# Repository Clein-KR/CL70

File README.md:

# CL70

<br />

CL70은 제가 자작을 시도하며 처음 만들었던 키보드입니다.

아무것도 모르는 채로 시작하여 겪어야 했던 수 많은 시행 착오를 다른 분들은 최대한 줄였으면 하는 마음에 해당 키보드를 리메이크 하는 내용으로 [나만의 커스텀 커스텀 키보드 만들기 시리즈](https://www.notion.so/clein-kr/27f2e6fbea69806facf0daf639f351d5)를 노션에 연재해 두었으니 자작 키보드에 관심이 있으신 분들은 한 번 읽어 보시는 것을 추천 드립니다.

<br />
<br />

**Silver Top**

<br />

**Black Top**

<br />
<br />

## Licence

<br />

작업물에 대한 영리적 목적의 사용 및 재배포는 허용하지 않으며, 비영리적 활동에만 사용 및 출처를 포함한 재배포를 허용합니다. 또한 작업물에 만약 오류나 문제가 있더라도 원작자는 이에 대해 어떠한 책임도 지지 않음을 미리 밝힙니다. 라이선스 전문은 [여기](./LICENCE)에서 보실 수 있습니다.

<br />
<br />

© 2026 [Clein](https://github.com/Clein-KR) All Rights Reserved. Licensed under [CC BY-NC 4.0](https://creativecommons.org/licenses/by-nc/4.0/)

<br />

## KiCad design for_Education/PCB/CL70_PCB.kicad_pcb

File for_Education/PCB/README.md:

# CL70 PCB for Education

<br />

<br />
<br />

## Licence

<br />

해당 프로젝트는 [ai03](https://github.com/ai03-2725) 님의 [KBD8X-MKII-PCB](https://github.com/ai03-2725/KBD8X-MKII-PCB) 프로젝트와 [Joe Scotto](https://github.com/joe-scotto) 님의 [ScottoKeebs](https://github.com/joe-scotto/scottokeebs) 프로젝트를 기반으로 만들어졌습니다. 해당 프로젝트를 활용한 수정, 복제, 배포 등의 활동은 저작자 표시와 함께 비영리적인 목적에 한해서만 가능하며, 라이선스 전문은 [여기](./LICENCE)에서 보실 수 있습니다.

<br />

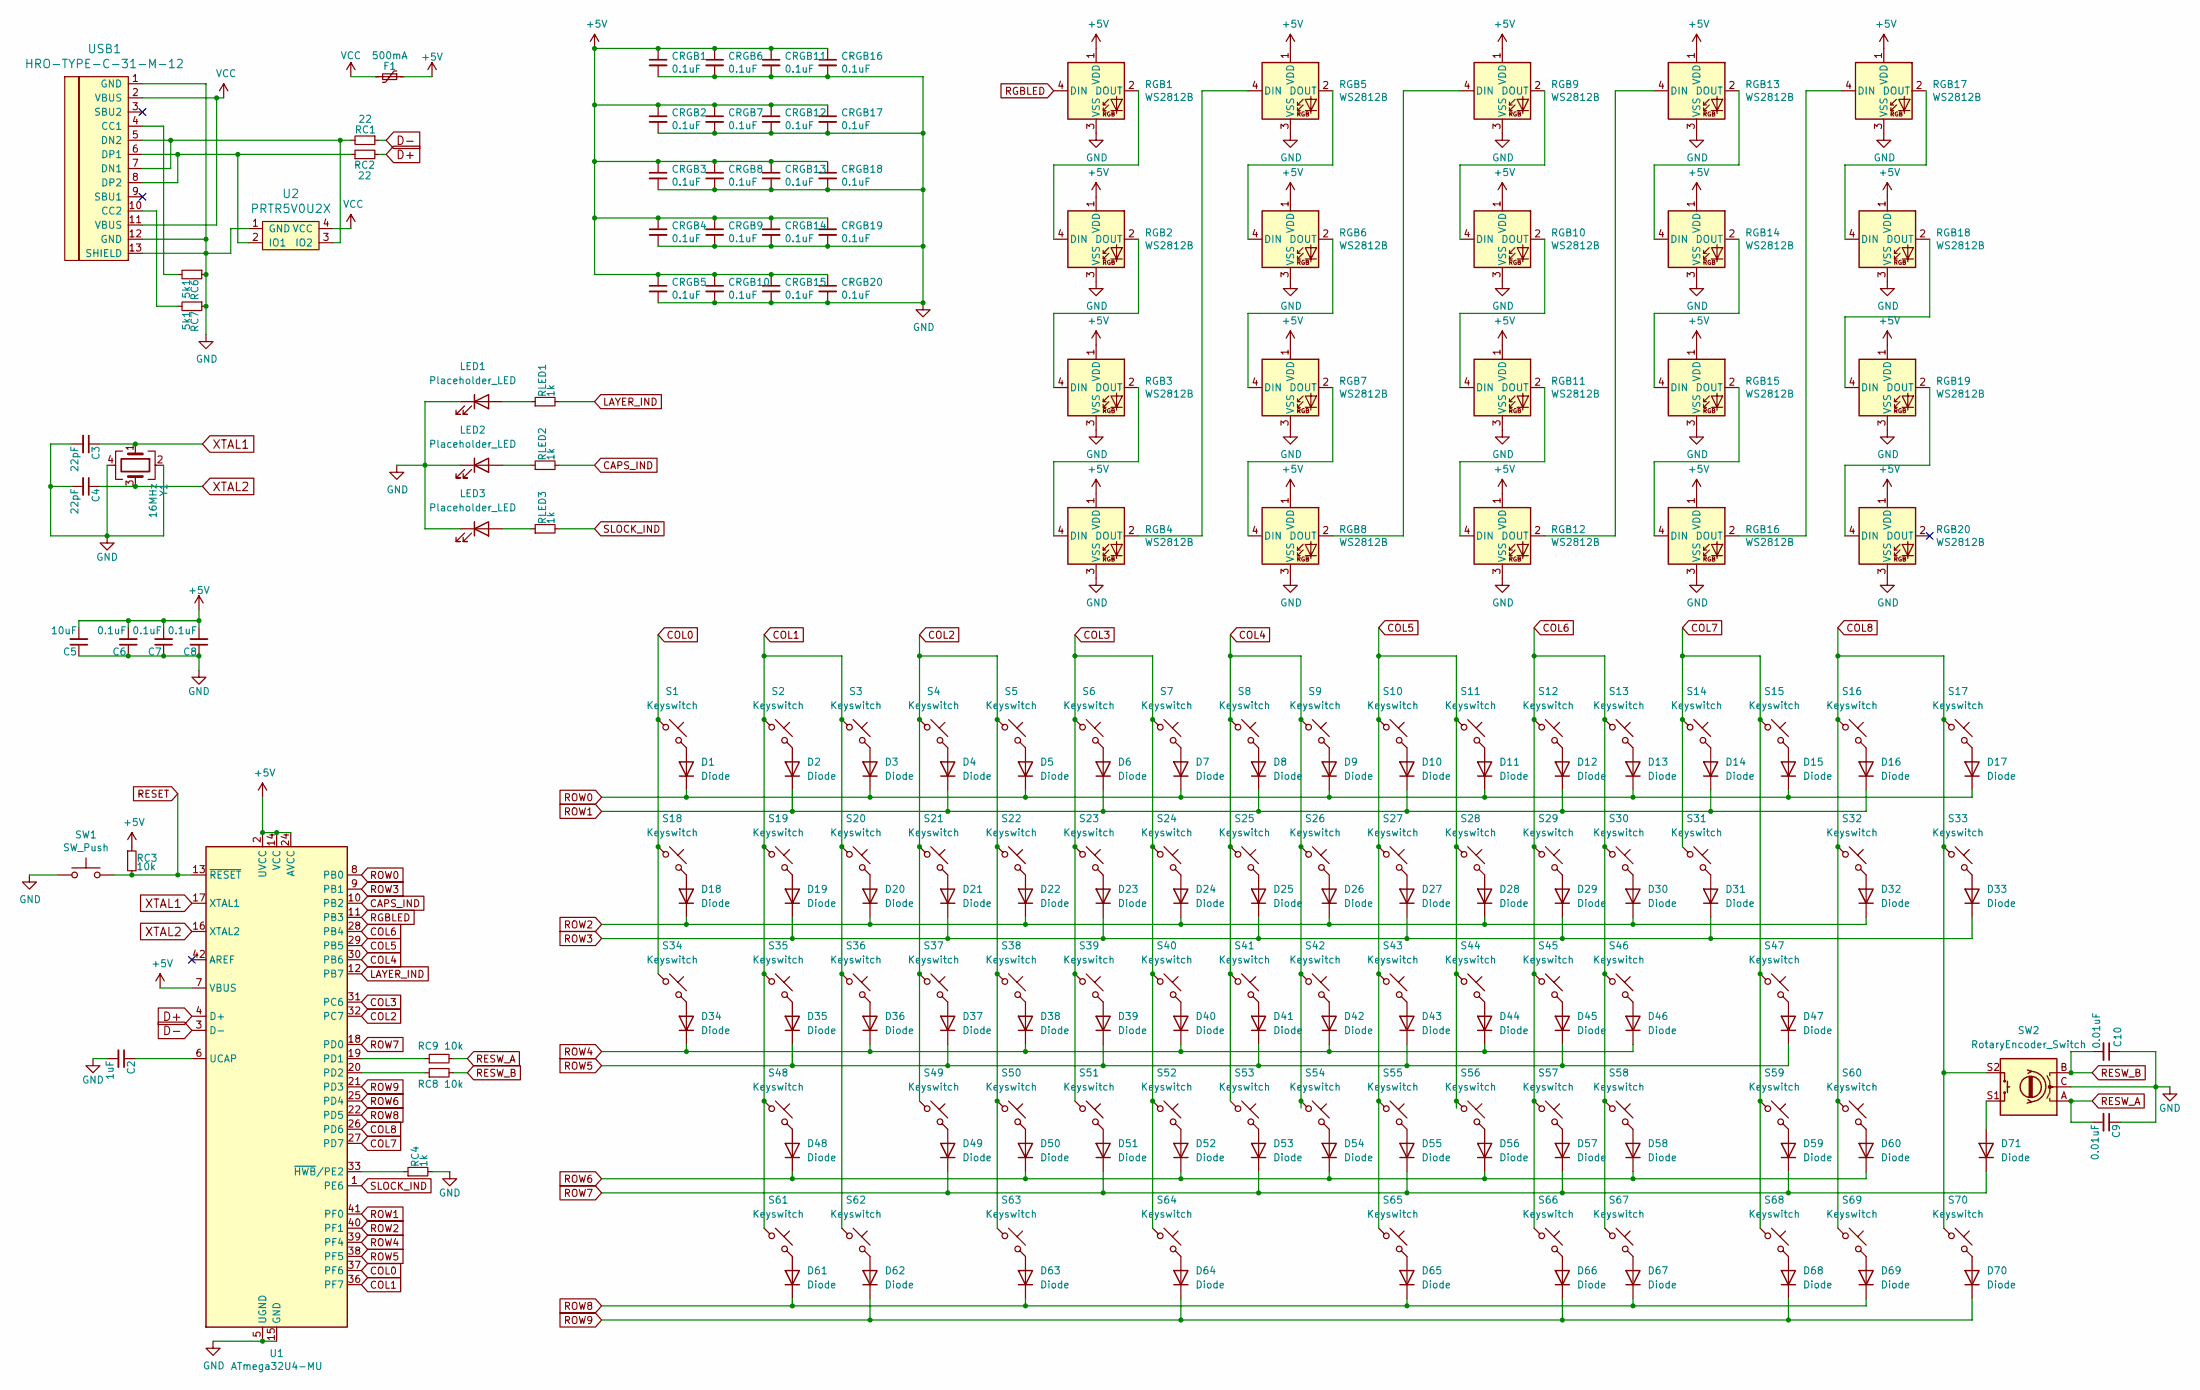
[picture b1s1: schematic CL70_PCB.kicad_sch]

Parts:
C2: 1uF; C_0603
C3, C4: 22pF; C_0603
C5: 10uF; C_0603
C6, C7, C8: 0.1uF; C_0603
C9, C10: 0.01uF; C_0603
CRGB1, CRGB2, CRGB3, CRGB4, CRGB5, CRGB6, CRGB7, CRGB8, CRGB9, CRGB10, CRGB11, CRGB12, CRGB13, CRGB14, CRGB15, CRGB16, CRGB17, CRGB18, CRGB19, CRGB20: 0.1uF; C_0603
D1, D2, D3, D4, D5, D6, D7, D8, D9, D10, D11, D12, D13, D14, D15, D16, D17, D18, D19, D20, D21, D22, D23, D24, D25, D26, D27, D28, D29, D30, D31, D32, D33, D34, D35, D36, D37, D38, D39, D40, D41, D42, D43, D44, D45, D46, D47, D48, D49, D50, D51, D52, D53, D54, D55, D56, D57, D58, D59, D60, D61, D62, D63, D64, D65, D66, D67, D68, D69, D70, D71: Diode; D_SOD-123
F1: 500mA; Fuse_1206_3216Metric
LED1, LED2, LED3: Placeholder_LED; LED_D3.0mm-Pretty
RC1, RC2: 22; R_0603
RC3, RC8, RC9: 10k; R_0603
RC4: 1k; R_0603
RC6, RC7: 5k1; R_0603
RGB1, RGB2, RGB3, RGB4, RGB5, RGB6, RGB7, RGB8, RGB9, RGB10, RGB11, RGB12, RGB13, RGB14, RGB15, RGB16, RGB17, RGB18, RGB19, RGB20: WS2812B; LED_WS2812B-PLCC4
RLED1, RLED2, RLED3: 1k; R_0603
S1, S2, S3, S4, S5, S6, S7, S8, S9, S10, S11, S12, S13, S14, S15, S16, S17, S18, S20, S21, S22, S23, S24, S25, S26, S27, S28, S29, S30, S31, S33, S34, S36, S37, S38, S39, S40, S41, S42, S43, S44, S45, S46, S49, S50, S51, S52, S53, S54, S55, S56, S57, S58, S60, S68, S69, S70: Keyswitch; MX_PCB_1.00u
S19, S32, S63, S66: Keyswitch; MX_PCB_1.50u
S35: Keyswitch; MX_PCB_1.75u
S47, S48: Keyswitch; Hotswap_MX_2.25u
S59: Keyswitch; Hotswap_MX_2.00u
S61, S62, S67: Keyswitch; MX_PCB_1.25u
S64, S65: Keyswitch; Hotswap_MX_3.00u
SW1: SW_Push; SKQG-1155865
SW2: RotaryEncoder_Switch; RotaryEncoder_Alps_EC11E-Switch_Vertical_H20mm
U1: ATmega32U4-MU; QFN-44-1EP_7x7mm_Pitch0.5mm
U2: PRTR5V0U2X; SOT143B
USB1: HRO-TYPE-C-31-M-12; HRO-TYPE-C-31-M-12-Assembly
Y1: 16MHz; Crystal_SMD_3225-4pin_3.2x2.5mm

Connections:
+5V: C5.2, C6.2, C7.2, C8.2, CRGB1.1, CRGB2.1, CRGB3.1, CRGB4.1, CRGB5.1, CRGB6.1, CRGB7.1, CRGB8.1, CRGB9.1, CRGB10.1, CRGB11.1, CRGB12.1, CRGB13.1, CRGB14.1, CRGB15.1, CRGB16.1, CRGB17.1, CRGB18.1, CRGB19.1, CRGB20.1, F1.1, RC3.1, RGB1.1 (VDD), RGB2.1 (VDD), RGB3.1 (VDD), RGB4.1 (VDD), RGB5.1 (VDD), RGB6.1 (VDD), RGB7.1 (VDD), RGB8.1 (VDD), RGB9.1 (VDD), RGB10.1 (VDD), RGB11.1 (VDD), RGB12.1 (VDD), RGB13.1 (VDD), RGB14.1 (VDD), RGB15.1 (VDD), RGB16.1 (VDD), RGB17.1 (VDD), RGB18.1 (VDD), RGB19.1 (VDD), RGB20.1 (VDD), U1.2 (UVCC), U1.7 (VBUS), U1.14 (VCC), U1.24 (AVCC), U1.34 (VCC), U1.44 (AVCC)
CAPS_IND: RLED2.2, U1.10 (PB2)
COL0: S1.1, S18.1, S34.1, U1.37 (PF6)
COL1: S2.1, S3.1, S19.1, S20.1, S35.1, S36.1, S48.1, S61.1, S62.1, U1.36 (PF7)
COL2: S4.1, S5.1, S21.1, S22.1, S37.1, S38.1, S49.1, S50.1, S63.1, U1.32 (PC7)
COL3: S6.1, S7.1, S23.1, S24.1, S39.1, S40.1, S51.1, S52.1, S64.1, U1.31 (PC6)
COL4: S8.1, S9.1, S25.1, S26.1, S41.1, S42.1, S53.1, S54.1, U1.30 (PB6)
COL5: S10.1, S11.1, S27.1, S28.1, S43.1, S44.1, S55.1, S56.1, S65.1, U1.29 (PB5)
COL6: S12.1, S13.1, S29.1, S30.1, S45.1, S46.1, S57.1, S58.1, S66.1, S67.1, U1.28 (PB4)
COL7: S14.1, S15.1, S31.1, S47.1, S59.1, S68.1, U1.27 (PD7)
COL8: S16.1, S17.1, S32.1, S33.1, S60.1, S69.1, S70.1, SW2.S2, U1.26 (PD6)
D+: RC2.2, U1.4 (D+)
D-: RC1.1, U1.3 (D-)
GND: C2.2, C3.2, C4.2, C5.1, C6.1, C7.1, C8.1, C9.1, C10.1, CRGB1.2, CRGB2.2, CRGB3.2, CRGB4.2, CRGB5.2, CRGB6.2, CRGB7.2, CRGB8.2, CRGB9.2, CRGB10.2, CRGB11.2, CRGB12.2, CRGB13.2, CRGB14.2, CRGB15.2, CRGB16.2, CRGB17.2, CRGB18.2, CRGB19.2, CRGB20.2, LED1.1 (K), LED2.1 (K), LED3.1 (K), RC4.2, RC6.1, RC7.1, RGB1.3 (VSS), RGB2.3 (VSS), RGB3.3 (VSS), RGB4.3 (VSS), RGB5.3 (VSS), RGB6.3 (VSS), RGB7.3 (VSS), RGB8.3 (VSS), RGB9.3 (VSS), RGB10.3 (VSS), RGB11.3 (VSS), RGB12.3 (VSS), RGB13.3 (VSS), RGB14.3 (VSS), RGB15.3 (VSS), RGB16.3 (VSS), RGB17.3 (VSS), RGB18.3 (VSS), RGB19.3 (VSS), RGB20.3 (VSS), SW1.1, SW2.C, U1.5 (UGND), U1.15 (GND), U1.23 (GND), U1.35 (GND), U1.43 (GND), U1.45 (GND), U2.1 (GND), USB1.1 (GND), USB1.12 (GND), USB1.13 (SHIELD), Y1.2, Y1.4
LAYER_IND: RLED1.2, U1.12 (PB7)
unnamed: D1.2 (A), S1.2
unnamed: D2.2 (A), S2.2
unnamed: D3.2 (A), S3.2
unnamed: D4.2 (A), S4.2
unnamed: D5.2 (A), S5.2
unnamed: D6.2 (A), S6.2
unnamed: D7.2 (A), S7.2
unnamed: D8.2 (A), S8.2
unnamed: D9.2 (A), S9.2
unnamed: D10.2 (A), S10.2
unnamed: D11.2 (A), S11.2
unnamed: D12.2 (A), S12.2
unnamed: D13.2 (A), S13.2
unnamed: D14.2 (A), S14.2
unnamed: D15.2 (A), S15.2
unnamed: D16.2 (A), S16.2
unnamed: D17.2 (A), S17.2
unnamed: D18.2 (A), S18.2
unnamed: D19.2 (A), S19.2
unnamed: D20.2 (A), S20.2
unnamed: D21.2 (A), S21.2
unnamed: D22.2 (A), S22.2
unnamed: D23.2 (A), S23.2
unnamed: D24.2 (A), S24.2
unnamed: D25.2 (A), S25.2
unnamed: D26.2 (A), S26.2
unnamed: D27.2 (A), S27.2
unnamed: D28.2 (A), S28.2
unnamed: D29.2 (A), S29.2
unnamed: D30.2 (A), S30.2
unnamed: D31.2 (A), S31.2
unnamed: D32.2 (A), S32.2
unnamed: D33.2 (A), S33.2
unnamed: D34.2 (A), S34.2
unnamed: D35.2 (A), S35.2
unnamed: D36.2 (A), S36.2
unnamed: D37.2 (A), S37.2
unnamed: D38.2 (A), S38.2
unnamed: D39.2 (A), S39.2
unnamed: D40.2 (A), S40.2
unnamed: D41.2 (A), S41.2
unnamed: D42.2 (A), S42.2
unnamed: D43.2 (A), S43.2
unnamed: D44.2 (A), S44.2
unnamed: D45.2 (A), S45.2
unnamed: D46.2 (A), S46.2
unnamed: D47.2 (A), S47.2
unnamed: D48.2 (A), S48.2
unnamed: D49.2 (A), S49.2
unnamed: D50.2 (A), S50.2
unnamed: D51.2 (A), S51.2
unnamed: D52.2 (A), S52.2
unnamed: D53.2 (A), S53.2
unnamed: D54.2 (A), S54.2
unnamed: D55.2 (A), S55.2
unnamed: D56.2 (A), S56.2
unnamed: D57.2 (A), S57.2
unnamed: D58.2 (A), S58.2
unnamed: D59.2 (A), S59.2
unnamed: D60.2 (A), S60.2
unnamed: D61.2 (A), S61.2
unnamed: D62.2 (A), S62.2
unnamed: D63.2 (A), S63.2
unnamed: D64.2 (A), S64.2
unnamed: D65.2 (A), S65.2
unnamed: D66.2 (A), S66.2
unnamed: D67.2 (A), S67.2
unnamed: D68.2 (A), S68.2
unnamed: D69.2 (A), S69.2
unnamed: D70.2 (A), S70.2
unnamed: D71.2 (A), SW2.S1
unnamed: LED1.2 (A), RLED1.1
unnamed: LED2.2 (A), RLED2.1
unnamed: LED3.2 (A), RLED3.1
unnamed: RGB1.2 (DOUT), RGB2.4 (DIN)
unnamed: RGB2.2 (DOUT), RGB3.4 (DIN)
unnamed: RGB3.2 (DOUT), RGB4.4 (DIN)
unnamed: RGB4.2 (DOUT), RGB5.4 (DIN)
unnamed: RGB5.2 (DOUT), RGB6.4 (DIN)
unnamed: RGB6.2 (DOUT), RGB7.4 (DIN)
unnamed: RGB7.2 (DOUT), RGB8.4 (DIN)
unnamed: RGB8.2 (DOUT), RGB9.4 (DIN)
unnamed: RGB9.2 (DOUT), RGB10.4 (DIN)
unnamed: RGB10.2 (DOUT), RGB11.4 (DIN)
unnamed: RGB11.2 (DOUT), RGB12.4 (DIN)
unnamed: RGB12.2 (DOUT), RGB13.4 (DIN)
unnamed: RGB13.2 (DOUT), RGB14.4 (DIN)
unnamed: RGB14.2 (DOUT), RGB15.4 (DIN)
unnamed: RGB15.2 (DOUT), RGB16.4 (DIN)
unnamed: RGB16.2 (DOUT), RGB17.4 (DIN)
unnamed: RGB17.2 (DOUT), RGB18.4 (DIN)
unnamed: RGB18.2 (DOUT), RGB19.4 (DIN)
unnamed: RGB19.2 (DOUT), RGB20.4 (DIN)
unnamed: RC9.1, U1.19 (PD1)
unnamed: RC8.1, U1.20 (PD2)
unnamed: C2.1, U1.6 (UCAP)
unnamed: RC4.1, U1.33 (~HWB/PE2)
unnamed: RC2.1, U2.2 (IO1), USB1.6 (DP1), USB1.8 (DP2)
unnamed: RC1.2, U2.3 (IO2), USB1.5 (DN2), USB1.7 (DN1)
unnamed: RC6.2, USB1.4 (CC1)
unnamed: RC7.2, USB1.10 (CC2)
RESET: RC3.2, SW1.2, U1.13 (~RESET)
RESW_A: C9.2, RC9.2, SW2.A
RESW_B: C10.2, RC8.2, SW2.B
RGBLED: RGB1.4 (DIN), U1.11 (PB3)
ROW0: D1.1 (K), D3.1 (K), D5.1 (K), D7.1 (K), D9.1 (K), D11.1 (K), D13.1 (K), D15.1 (K), D17.1 (K), U1.8 (PB0)
ROW1: D2.1 (K), D4.1 (K), D6.1 (K), D8.1 (K), D10.1 (K), D12.1 (K), D14.1 (K), D16.1 (K), U1.41 (PF0)
ROW2: D18.1 (K), D20.1 (K), D22.1 (K), D24.1 (K), D26.1 (K), D28.1 (K), D30.1 (K), D32.1 (K), U1.40 (PF1)
ROW3: D19.1 (K), D21.1 (K), D23.1 (K), D25.1 (K), D27.1 (K), D29.1 (K), D31.1 (K), D33.1 (K), U1.9 (PB1)
ROW4: D34.1 (K), D36.1 (K), D38.1 (K), D40.1 (K), D42.1 (K), D44.1 (K), D46.1 (K), U1.39 (PF4)
ROW5: D35.1 (K), D37.1 (K), D39.1 (K), D41.1 (K), D43.1 (K), D45.1 (K), D47.1 (K), U1.38 (PF5)
ROW6: D48.1 (K), D50.1 (K), D52.1 (K), D54.1 (K), D56.1 (K), D58.1 (K), D60.1 (K), U1.25 (PD4)
ROW7: D49.1 (K), D51.1 (K), D53.1 (K), D55.1 (K), D57.1 (K), D59.1 (K), D71.1 (K), U1.18 (PD0)
ROW8: D61.1 (K), D63.1 (K), D65.1 (K), D67.1 (K), D69.1 (K), U1.22 (PD5)
ROW9: D62.1 (K), D64.1 (K), D66.1 (K), D68.1 (K), D70.1 (K), U1.21 (PD3)
SLOCK_IND: RLED3.2, U1.1 (PE6)
VCC: F1.2, U2.4 (VCC), USB1.2 (VBUS), USB1.11 (VBUS)
XTAL1: C3.1, U1.17 (XTAL1), Y1.1
XTAL2: C4.1, U1.16 (XTAL2), Y1.3

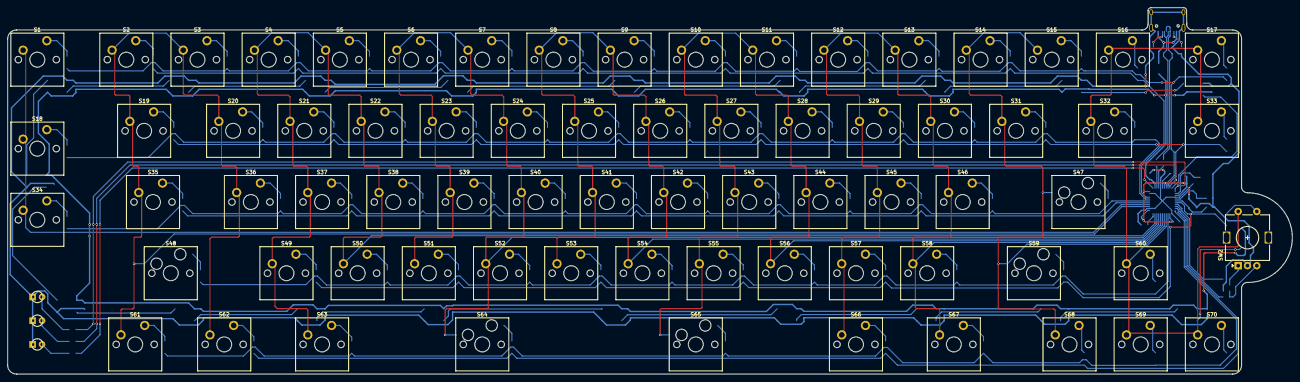
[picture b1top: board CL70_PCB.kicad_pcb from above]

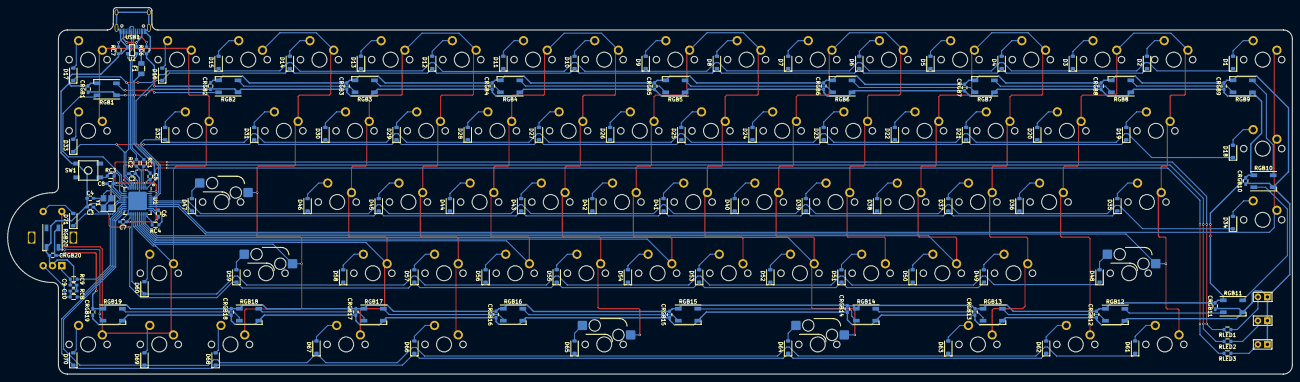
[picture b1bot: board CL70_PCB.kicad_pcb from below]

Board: 2 copper layers, 343.8 x 98.1 mm, 211 parts (137 on the bottom side), 134 nets.

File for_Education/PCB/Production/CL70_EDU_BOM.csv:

,,,,,,,,,,
,Item #,*Designator,*Qty,Manufacturer,*Mfg Part #,LCSC Part #,Description / Value,*Package/Footprint,Pins,Your Instructions / Notes
,1,"C6,C7,C8,CRGB1,CRGB2,CRGB3,CRGB4,CRGB5,CRGB6,CRGB7,CRGB8,CRGB9,CRGB10,CRGB11,CRGB12,CRGB13,CRGB14,CRGB15,CRGB16,CRGB17,CRGB18,CRGB19,CRGB20",23,YAGEO,CC0603JRX7R7BB104,C109474,"Capacitor, Ceramic, 0603",C_0603,2,0.1uF 20% ≥15V X5R/X7R
,2,C5,1,HRE,CGA0603X5R106M160JT,C6119814,"Capacitor, Ceramic, 0603",C_0603,2,10uF 20% ≥15V X5R/X7R
,3,C2,1,HRE,CGA0603X5R105K160JT,C6119849,"Capacitor, Ceramic, 0603",C_0603,2,1uF 20% ≥15V X5R/X7R
,4,"C3,C4",2,KEMET,C0603C220J4GAC7867,C561800,"Capacitor, Ceramic, 0603",C_0603,2,22pF 5% ≥15V C0G
,5,"D1,D2,D3,D4,D5,D6,D7,D8,D9,D10,D11,D12,D13,D14,D15,D16,D17,D18,D19,D20,D21,D22,D23,D24,D25,D26,D27,D28,D29,D30,D31,D32,D33,D34,D35,D36,D37,D38,D39,D40,D41,D42,D43,D44,D45,D46,D47,D48,D49,D50,D51,D52,D53,D54,D55,D56,D57,D58,D59,D60,D61,D62,D63,D64,D65,D66,D67,D68,D69,D70,D71",71,Slkor(SLKORMICRO Elec.),1N4148W,C444720,"Diode, SOD-123",D_SOD-123,2,Generic
,6,F1,1,BHFUSE,BSMD1206-050-16V,C883124,"Polyfuse, 1206",Fuse_SMD1206_Wave,2,500mA ≥15V 500mA_Hold 1A_Trip
,7,"RC4,RLED1,RLED2,RLED3",4,YAGEO,RC0603FR-071KL,C22548,"Resistor, Generic, 0603",R_0603,2,1k 1%
,8,"RC3,RC8,RC9",3,YAGEO,RC0603FR-0710KL,C98220,"Resistor, Generic, 0603",R_0603,2,10k 1%
,9,"RC1,RC2",2,YAGEO,RC0603FR-0722RL,C107701,"Resistor, Generic, 0603",R_0603,2,22 1%
,10,"RC6,RC7",2,YAGEO,RC0603FR-075K1L,C105580,"Resistor, Generic, 0603",R_0603,2,5.1k 1%
,11,"RGB1,RGB2,RGB3,RGB4,RGB5,RGB6,RGB7,RGB8,RGB9,RGB10,RGB11,RGB12,RGB13,RGB14,RGB15,RGB16,RGB17,RGB18,RGB19,RGB20",20,Worldsemi,WS2812B-V5/W,C2874885,"RGB LED, 5050",LED_WS2812B-PLCC4,4,WS2812B
,12,SW1,1,ALPSALPINE,SKQGABE010,C115351,Push button,SKQG-1155865,4,SMT 5.2 x 5.2 x 1.5mm
,13,U1,1,MICROCHIP,ATMEGA32U4-MU,C112161,ATmega32U4-MU,QFN-44-1EP_7x7mm_Pitch0.5mm,45,ATmega32U4-MU
,14,U2,1,Nexperia,"PRTR5V0U2X,215",C12333,ESD Protection IC,SOT143B,4,PRTR5V0U2X
,15,USB1,1,Korean Hroparts Elec,TYPE-C-31-M-12,C165948,USB Type-C Connector,HRO-TYPE-C-31-M-12-Assembly,16,HRO-TYPE-C-31-M-12
,16,Y1,1,Huiyuan crystal,HY16MSMD3225OB1R30,C7275098,"Crystal, 3.2 x 2.5mm (3225-4)",Crystal_SMD_3225-4pin_3.2x2.5mm,4,16MHz

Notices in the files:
for_Education/PCB/README.md:
https://mirrors.creativecommons.org/presskit/icons/cc.svg?ref=chooser-v1
https://mirrors.creativecommons.org/presskit/icons/by.svg?ref=chooser-v1
https://mirrors.creativecommons.org/presskit/icons/nc.svg?ref=chooser-v1
https://mirrors.creativecommons.org/presskit/icons/sa.svg?ref=chooser-v1
